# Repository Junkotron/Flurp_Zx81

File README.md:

# "Flurp zx81" on an fpga lots of stuff borrowed from "Blackice MX ZX81"
# Now for use on the Olimex ice40 8k board.

Second release some cleanup done but some elephants still remain

Features so far of the "Flurp"

* 16k or 1k ZX81 running at 3.2MHz
* PAL/NTSC output
* mic/ear/line for playing and recording sound files
* PS/2 keyboard connector (works with most USB keyboards)
* A debug port for a logic analyzer
* Serial port can now fairly reliably quick load programs
* 5 volt in from mobile charger, USB or similar

"Flurp" PCB drawings in kicad all in 0.1" grid so "banana finger" is no excuse
anymore, all hole-mounted like in the old days. If you, like me, fiddled
together a Zeddy at twelve you should be able to do this. Actually it is 
easier since no nerve-wrecking 40 pinners need be pressed in their sockets.
Components as far as I know can still be obtained, caps, connectors,
resistors and a single diode for over-voltage from the cassette interface
(could be omitted for the brave at heart).

First PCB is "in the air" as of this writing.

Since there is so many ideas of the connectors I made them as simple
pin and hole headers so there is no on-board fittings for RCA-jacks, 3.5mm
keyboard or similar since the chance of you obtaining whatever I got hold
of would be near-zero, just dive into that junkbox you got and see what
pops up!
I assume anyone attempting this should know their way around old-timer
connectors or if you are younger, wikipedia and google for info
on antiques :)

ZX81 currently only with 1k or 16k config, one major improvement with the
Olimex board is its 512k SRAM which we can use as we like.
Most other boards have SDRAM and although this probably also can
be made working I leave it as an excercise to the experts.
Currently only 16k is used. Plans to move the ROM here as well, this
currently resides in the internal FPGA memory.

As when mentioning the ROM I sucessfully replaced the original ROM with
the infamous "ASZMIC" rom image and got the example from the manual
working (see aszmic.sh in speedloader/) 

There is also an example of where the virtual keyboard produces a really
long 10 REM ... line suitable for storing machine code, in the old days
this would make your thumb go numb since this old piece of antique did not
have key repeat..

A composite output, there is an unfortunate "panache" with a wobble
on the first text line, dont know if this is due to the almost-PAL nature
of the ZX81 or something introduced later on. I tried a modulator (VHF) 
of some cheap no-brand type which would actually feed an older flatscreen
I got. Seems the really new flat screens cannot do PAL/NTSC anymore.
Not tried on a real fat-TV or monitor yet.

An "ear" input, changes from Sinclair original is some pulldown I seemed
to need on the FPGA side and some cowardly added zener 3.3 volts since
the FPGA is not 5v tolerant like the original ULA.

A "line" output, this is to be fed into a line input of some kind of PC 
soundblaster, I used the "aplay/arecord" utilities on Linux to act as the
tape recorder, it actually worked more or less out of the box.
I also added a modified bandbass filter for the line level that aims
as "doing the same thing" as the original "mic" circuitry but with a higher
level.

A PS/2 keyboard input with some resistors again to adapt to the
3.3 volt logic. It also works on most USB keyboards I tried, forcing them
into legacy PS/2 mode with some pullups.
If you take the usb connector, the wires in the schematic should align with
how the physical usb port is layed out so you can start with the plus which
use to be red and then work your way into whatever connector you have available
You could also get a PS/2 keyboard on ebay though this more obvious option
has not been tested.

The 34-pole connector for the FPGA module (Olimex) note that the notch in
the FPGA boards connector should face the nearest rim of the pcb, there is a 
"Notch!" silk screen marker. I'm not in any way a professional cad:er so
I may have broken some standard ways of working concerning the connectors.
Possibly you will use a female 0.1" headers with no notch. I found that
adding a small dot of hot glue, let it cool off some and then press the
module on will "mold" a notch without clogging the fpga board with glue.
This "notch" has been quite useful for avoiding gray smoke.

A "mic" output, this is made according to the originals but has as of yet
not worked. I added a 5 volt feed in case someone wants to try to make some
analog adaptions to it, I tried to amplify the signal with a 741 but to
no avail. Have not tested with a "real" tape recorder will do that when I
get a hold of one and some tape.

Some games require you to have only 1k so there is a connector that will
downgrade the Flurp to 1k after a reset, otherwise poking RAMTOP should
work for most such games.

Another connector will pull the "pin 22" on the "ULA" high which should
give you NTSC format, this is untested so far. In the old days most
american TV-sets would eat the PAL signal just as well.

Loading old games, I have been successful in using the "zx81putil" for
converting the p-file games available into wav files and then playing them
via the line-out of my PC sound blaster into the "ear" of the Flurp

.. Below here is some cool stuff that is not really necessary
.. these connectors can be omitted

A connector for a six-pin serial module which is popular with Arduinos
and similar. Now the speedloader is working and also you can "remote
type" on the ZX81 keyboard.

The olimex 32u4 or similar is used for programming the SPI flash of the
FPGA, we sometimes need to reset the FPGA, this can be done with the
reset button on the olimex ice40 board itself or with for instance
> sudo iceprogduino -t
Which reads the flash ID (but also does a full reset much faster than a full
 reprogram)

Speedloader can now both produce load files and fast load them
Check out "speedloader.txt" for more info

A way to run the ZX keyboard from this serial port is now implemented
the speeloader/keysend.c can be used to primitively execute commands
on the flurp, such as 'RUN' 'LOAD ""' 'NEW' etc.

A 10-pin connector for a Logic Probe, dirt cheap and really useful if you
want to dive into the FPGA firmware.

Thats all for now!

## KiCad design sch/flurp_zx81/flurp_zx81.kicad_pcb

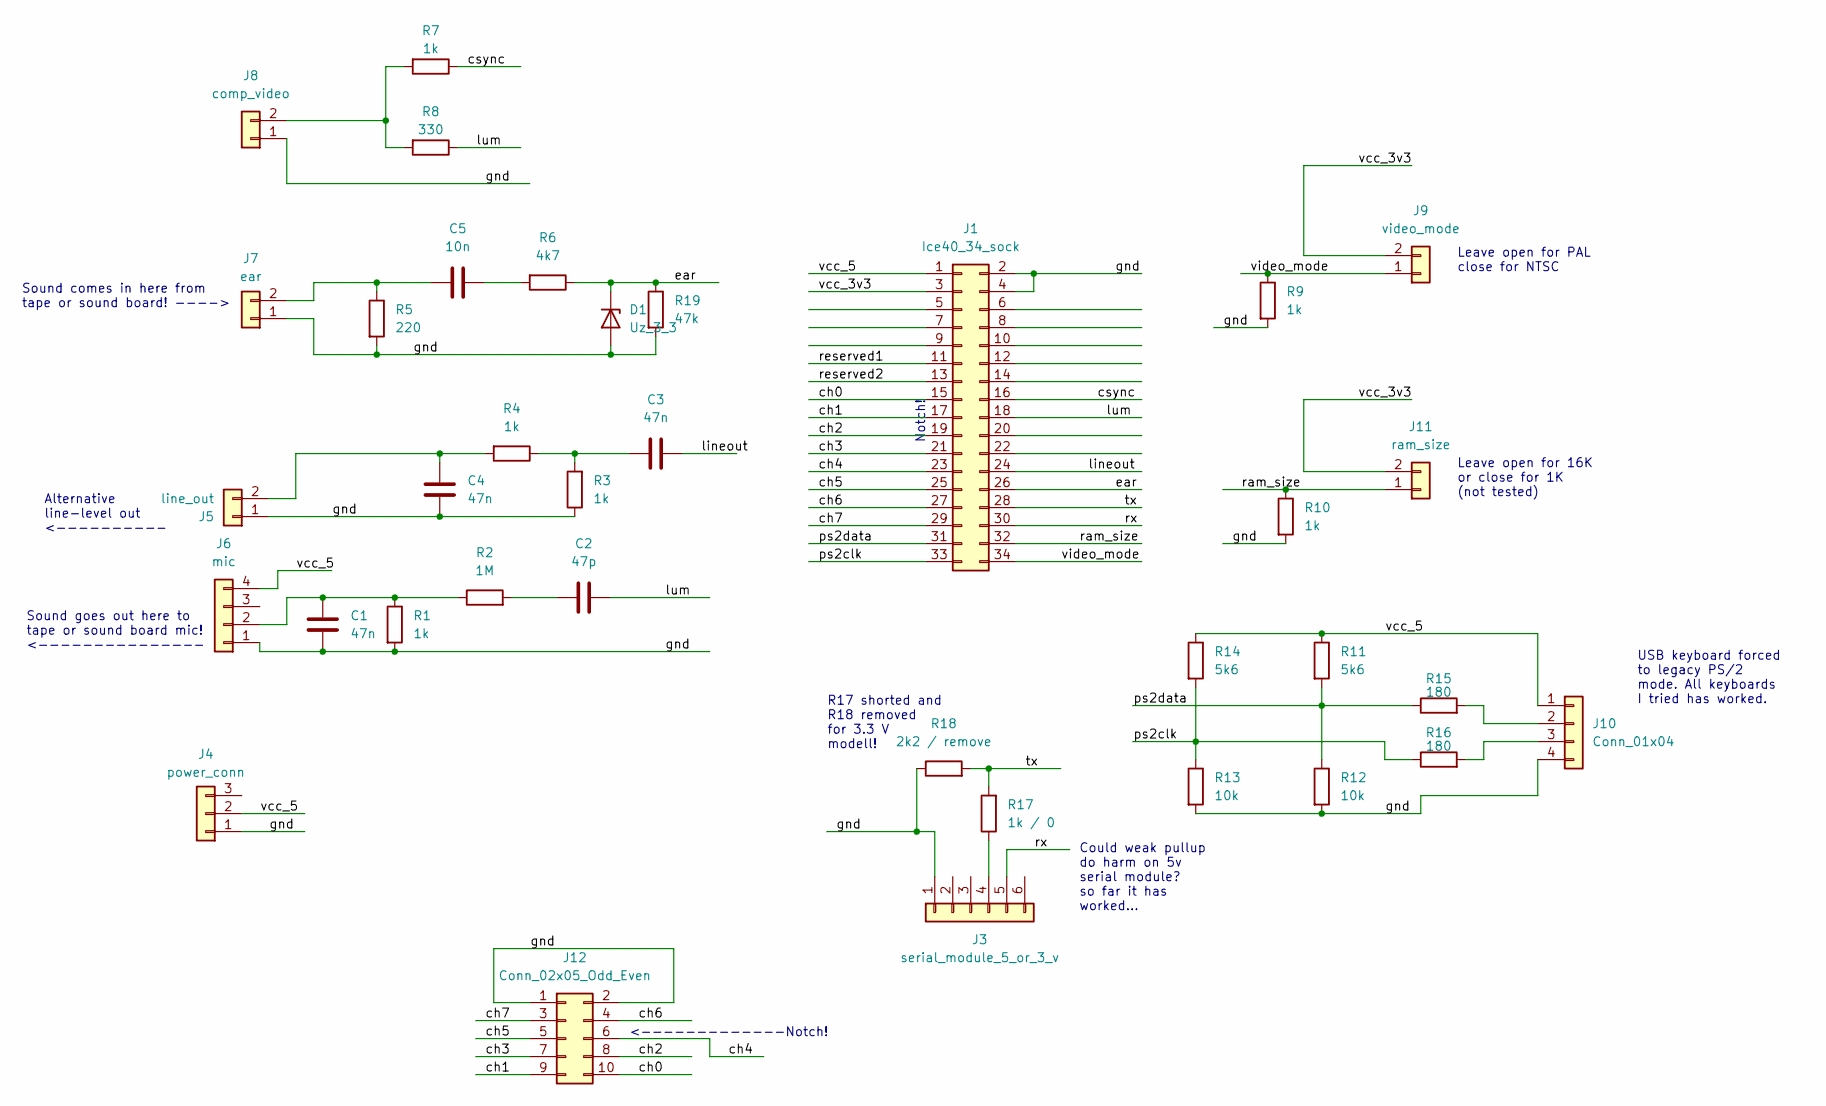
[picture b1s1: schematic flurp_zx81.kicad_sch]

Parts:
C1, C3, C4: 47n; C_Disc_D4.3mm_W1.9mm_P5.00mm
C2: 47p; C_Disc_D4.3mm_W1.9mm_P5.00mm
C5: 10n; C_Disc_D4.3mm_W1.9mm_P5.00mm
D1: Uz_3_3; R_Axial_DIN0204_L3.6mm_D1.6mm_P7.62mm_Horizontal
J1: Ice40_34_sock; PinSocket_2x17_P2.54mm_Vertical
J3: serial_module_5_or_3_v; PinSocket_1x06_P2.54mm_Vertical
J4: power_conn; PinHeader_1x03_P2.54mm_Vertical
J5: line_out; PinHeader_1x02_P2.54mm_Vertical
J6: mic; PinHeader_1x04_P2.54mm_Vertical
J7: ear; PinHeader_1x02_P2.54mm_Vertical
J8: comp_video; PinHeader_1x02_P2.54mm_Vertical
J9: video_mode; PinHeader_1x02_P2.54mm_Vertical
J10: Conn_01x04; PinHeader_1x04_P2.54mm_Vertical
J11: ram_size; PinHeader_1x02_P2.54mm_Vertical
J12: Conn_02x05_Odd_Even; PinSocket_2x05_P2.54mm_Vertical
R1, R3, R4, R7, R9, R10: 1k; R_Axial_DIN0204_L3.6mm_D1.6mm_P7.62mm_Horizontal
R2: 1M; R_Axial_DIN0204_L3.6mm_D1.6mm_P7.62mm_Horizontal
R5: 220; R_Axial_DIN0204_L3.6mm_D1.6mm_P7.62mm_Horizontal
R6: 4k7; R_Axial_DIN0204_L3.6mm_D1.6mm_P7.62mm_Horizontal
R8: 330; R_Axial_DIN0204_L3.6mm_D1.6mm_P7.62mm_Horizontal
R11, R14: 5k6; R_Axial_DIN0204_L3.6mm_D1.6mm_P7.62mm_Horizontal
R12, R13: 10k; R_Axial_DIN0204_L3.6mm_D1.6mm_P7.62mm_Horizontal
R15, R16: 180; R_Axial_DIN0204_L3.6mm_D1.6mm_P7.62mm_Horizontal
R17: 1k / 0; R_Axial_DIN0204_L3.6mm_D1.6mm_P7.62mm_Horizontal
R18: 2k2 / remove; R_Axial_DIN0204_L3.6mm_D1.6mm_P7.62mm_Horizontal
R19: 47k; R_Axial_DIN0204_L3.6mm_D1.6mm_P7.62mm_Horizontal

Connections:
/ch0: J1.15, J12.10
/ch1: J1.17, J12.9
/ch2: J1.19, J12.8
/ch3: J1.21, J12.7
/ch4: J1.23, J12.6
/ch5: J1.25, J12.5
/ch6: J1.27, J12.4
/ch7: J1.29, J12.3
/csync: J1.16, R7.1
/ear: D1.1 (K), J1.26, R6.1, R19.1
/gnd: C1.2, C4.1, D1.2 (A), J1.2, J1.4, J3.1, J4.1, J5.1, J6.1, J7.1, J8.1, J10.4, J12.1, J12.2, R1.2, R3.1, R5.2, R9.2, R10.2, R12.2, R13.2, R18.1, R19.2
/lineout: C3.2, J1.24
/lum: C2.2, J1.18, R8.1
/ps2clk: J1.33, R13.1, R14.2, R16.1
/ps2data: J1.31, R11.2, R12.1, R15.1
/ram_size: J1.32, J11.1, R10.1
/reserved1: J1.11
/reserved2: J1.13
/rx: J1.30, J3.5
/tx: J1.28, R17.2, R18.2
/vcc_3v3: J1.3, J9.2, J11.2
/vcc_5: J1.1, J4.2, J6.4, J10.1, R11.1, R14.1
/video_mode: J1.34, J9.1, R9.1
unnamed: C2.1, R2.2
unnamed: C3.1, R3.2, R4.1
unnamed: C5.2, R6.2
unnamed: J3.4, R17.1
unnamed: C4.2, J5.2, R4.2
unnamed: C1.1, J6.2, R1.1, R2.1
unnamed: C5.1, J7.2, R5.1
unnamed: J8.2, R7.2, R8.2
unnamed: J10.2, R15.2
unnamed: J10.3, R16.2

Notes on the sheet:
Sound goes out here to tape or sound board mic! <---------------
R17 shorted and R18 removed for 3.3 V modell!
Alternative line-level out <----------
<-------------Notch!
USB keyboard forced to legacy PS/2 mode. All keyboards I tried has worked.
Leave open for 16K or close for 1K (not tested)
Notch!
Could weak pullup do harm on 5v serial module? so far it has worked...
Leave open for PAL close for NTSC
Sound comes in here from tape or sound board! ---->

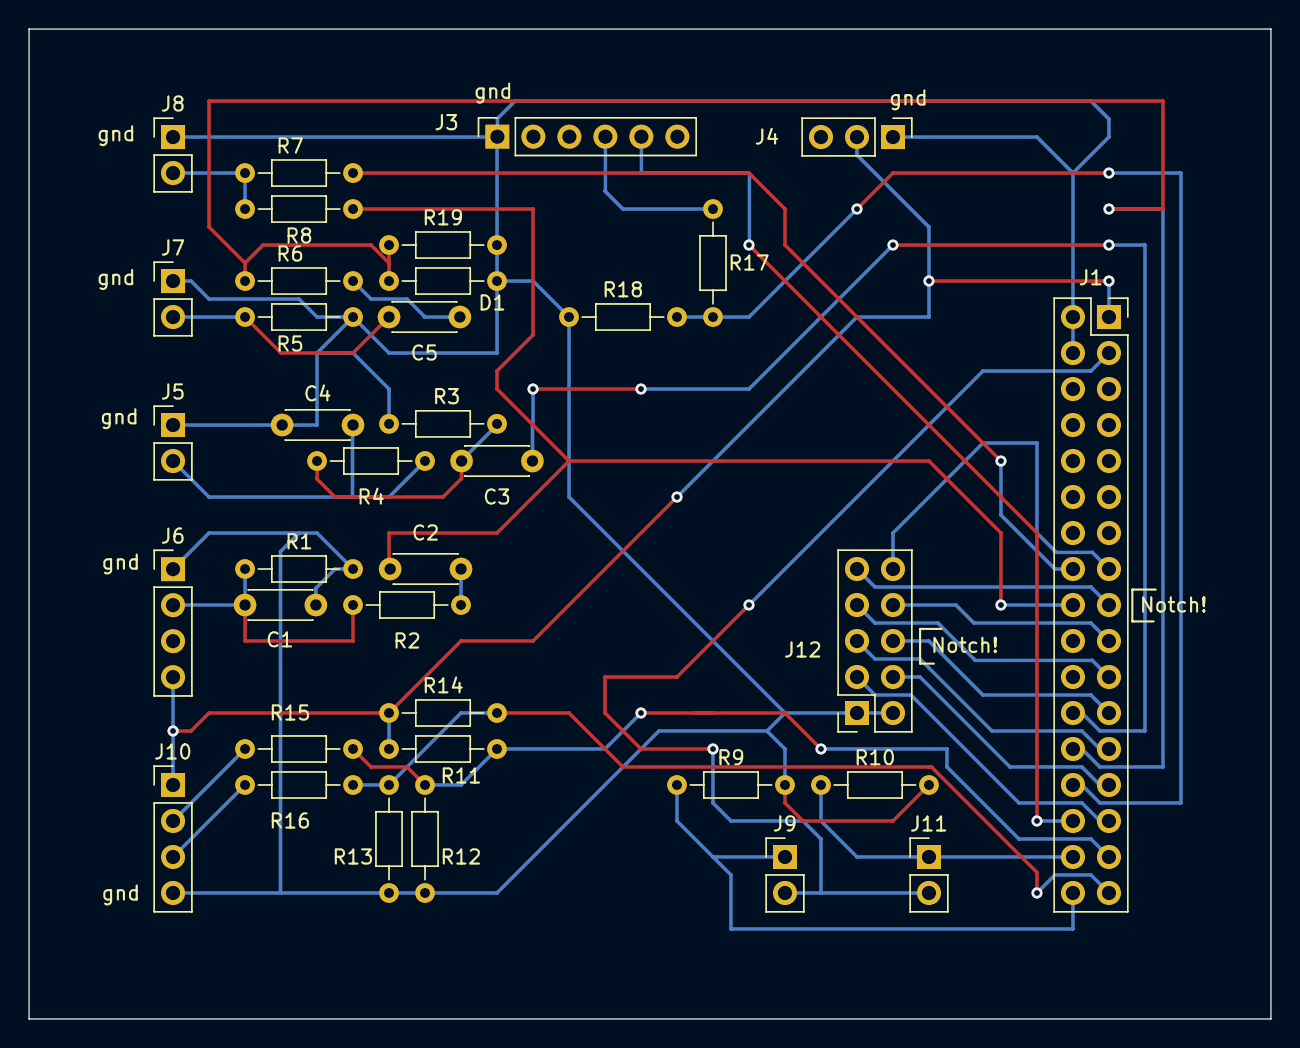
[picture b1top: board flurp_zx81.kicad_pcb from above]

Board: 2 copper layers, 87.6 x 69.8 mm, 36 parts (0 on the bottom side), 31 nets.

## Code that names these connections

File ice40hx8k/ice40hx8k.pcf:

# User Constraint File for BlackIcei Mx Acorn Atom (Ice40Atom)

# Onboard 25MHz oscillator
set_io clk_100mhz J3

set_io led1 M12
set_io led2 R16

set_io but1 K11
set_io but2 P13

# Physical config switches
set_io video_mode F3
set_io ram_size H3

# Keyboard - Matches Digilent PmodPS/2 
set_io ps2_clk           G3 #
set_io ps2_data          E2 # 

set_io csync J5
set_io lum H2

set_io ear F1

# This is actually "line out", mic shares with video pin zx original style
set_io mic H4

# VGA Output - Matches Digilent PmodVGA
#set_io red[3]           E4 # 
#set_io red[2]           R2 # 
#set_io red[1]           N5 #
#set_io red[0]           T2 # 

#set_io green[3]         B2 # 
#set_io green[2]         P5 # 
#set_io green[1]         R3 # 
#set_io green[0]         R5 # 

#set_io blue[3]          F5 # 
#set_io blue[2]          T3 # 
#set_io blue[1]          R4 # 
#set_io blue[0]          M7 # 

# ext 16k mem
set_io cs_n T6
set_io oe_n L9
set_io we_n T7


set_io a[0] N6
set_io a[1] T1
set_io a[2] P4
set_io a[3] R2
set_io a[4] N5
set_io a[5] T2
set_io a[6] P5
set_io a[7] R3
set_io a[8] R5
set_io a[9] T3
set_io a[10] R4
set_io a[11] M7
set_io a[12] N7
set_io a[13] P6
set_io a[14] M8
set_io a[15] T5
set_io a[16] R6
set_io a[17] P8

set_io d[0] T8
set_io d[1] P7
set_io d[2] N9
set_io d[3] T9
set_io d[4] M9
set_io d[5] R9
set_io d[6] K9
set_io d[7] P9


#set_io dbg_key[0] C2 # 
#set_io dbg_key[1] F4 # 
#set_io dbg_key[2] D2 # 
#set_io dbg_key[3] G5 # 
#set_io dbg_key[4] D1 # 
#set_io dbg_key[5] G4 # 
#set_io dbg_key[6] E3 # 
#set_io dbg_key[7] H5 # 

# salae port
# testch0 C2 # 
# testch1 F4 # 
# testch2 D2 # 
# testch3 G5 # 
# testch4 D1 # 
# testch5 G4 # 
# testch6 E3 # 
# testch7 H5 # 


# salae port
set_io testch[0] C2 # 
set_io testch[1] F4 # 
set_io testch[2] D2 # 
set_io testch[3] G5 # 
set_io testch[4] D1 # 
set_io testch[5] G4 # 
set_io testch[6] E3 # 
set_io testch[7] H5 # 

# Serial port monitor
set_io rx F2 # receives to serial adaptor
set_io tx H6 # sends from serial adaptor

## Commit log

2024-03-27 add initial readme
2024-03-27 initial add of what i think is all
2024-03-27 grammar
2024-03-27 wrong placed files
2024-03-27 some more docs
2024-03-27 added pdf:s for ease of access
2024-03-27 added leg conf
2024-04-11 release with new binary speed loader
2024-04-11 obsolete
2024-04-11 speed loader doc
2024-04-11 as my english teacher once put it, 'I'm sure you can spell two'
2024-04-11 addded prefab blobs for hard to master tools
2024-04-11 remove junk
